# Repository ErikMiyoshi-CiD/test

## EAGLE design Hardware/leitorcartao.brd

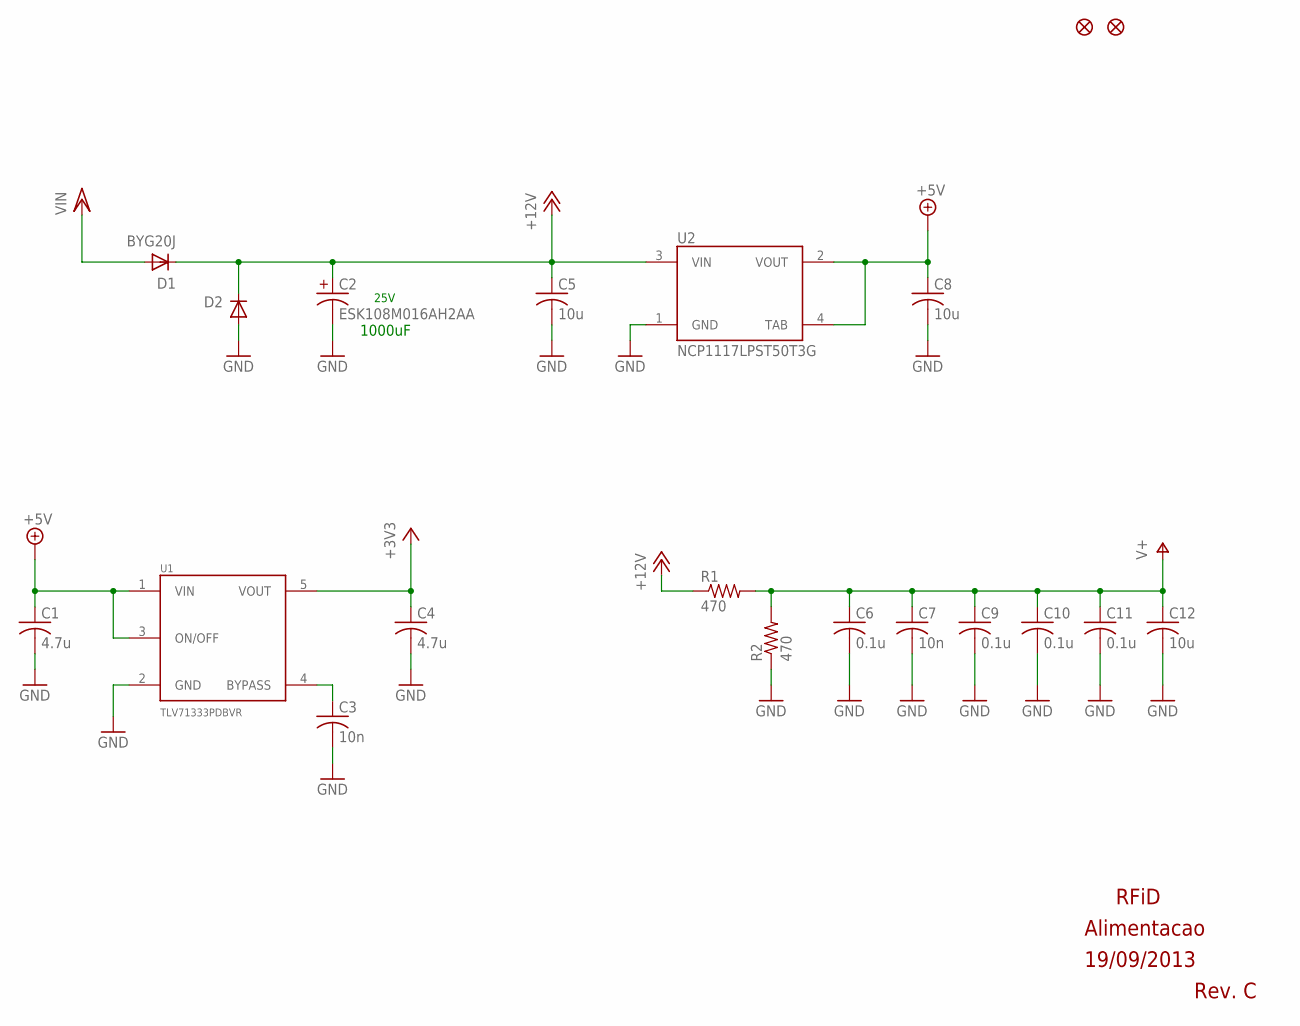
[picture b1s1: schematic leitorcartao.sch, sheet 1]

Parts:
C1, C4: 4.7u; C0603
C2: ESK108M016AH2AA
C3, C7: 10n; C0402
C5, C8, C12: 10u; C0805
C6, C9, C10, C11: 0.1u; C0402
D1: BYG20J; SMA
D2: DIODE-DO214AC; DO214AC
FID1, FID3: FIDUCIAL1.5X3; FIDUCIAL-1.5X3
R1, R2: 470; R0402
U1: TLV71333PDBVR; SOT-23-5
U2: NCP1117LPST50T3G; SOT223-3L

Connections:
+3V3: C4.1, U1.5 (VOUT); also elsewhere on the board
+5V: C1.1, C8.1, U1.1 (VIN), U1.3 (ON/OFF), U2.2 (VOUT), U2.4 (TAB); also elsewhere on the board
+12V: C2.+, C5.1, D1.K, D2.C, R1.1, U2.3 (VIN); also elsewhere on the board
GND: C1.2, C2.-, C3.2, C4.2, C5.2, C6.2, C7.2, C8.2, C9.2, C10.2, C11.2, C12.2, D2.A, R2.1, U1.2 (GND), U2.1 (GND); also elsewhere on the board
unnamed: C3.1, U1.4 (BYPASS)
V+: C6.1, C7.1, C9.1, C10.1, C11.1, C12.1, R1.2, R2.2; also elsewhere on the board
VCC/2: D1.A; also elsewhere on the board

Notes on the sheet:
RFiD
19/09/2013
Alimentacao
25V
1000uF
Rev. C

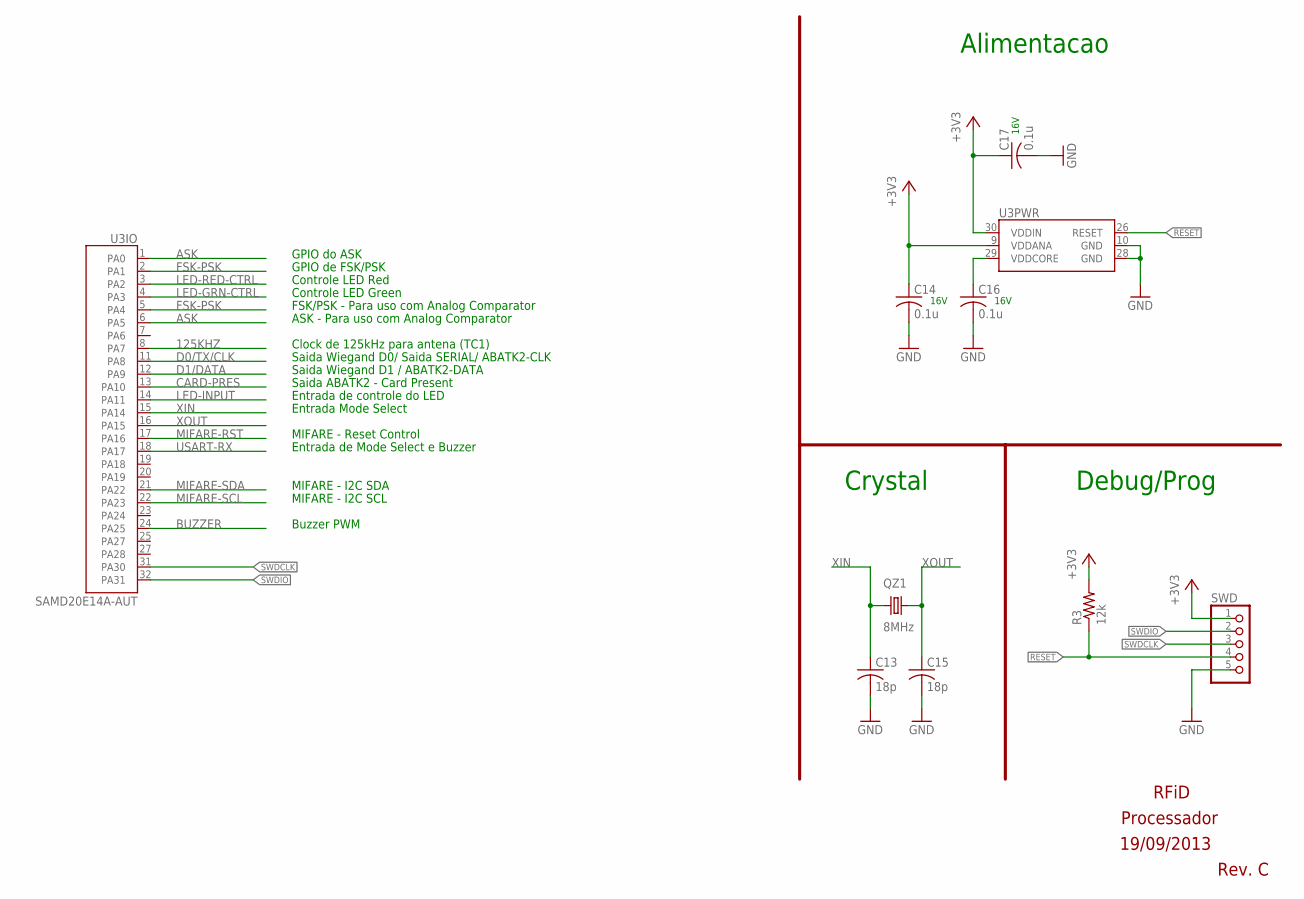
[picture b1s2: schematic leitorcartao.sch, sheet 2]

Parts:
C13, C15: 18p; C0603
C14, C16, C17: 0.1u; C0402
QZ1: 8MHz; HC49/S
R3: 12k; R0402
SWD: PINHD-1X5; 1X05
U3: SAMD20E14A-AUT; TQFP32

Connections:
125KHZ: U3.8 (PA7); also elsewhere on the board
+3V3: C14.1, C17.1, R3.2, SWD.1, U3.9 (VDDANA), U3.30 (VDDIN); also elsewhere on the board
ASK: U3.1 (PA0), U3.6 (PA5); also elsewhere on the board
BUZZER: U3.24 (PA25); also elsewhere on the board
CARD-PRES: U3.13 (PA10); also elsewhere on the board
D0/TX/CLK: U3.11 (PA8); also elsewhere on the board
D1/DATA: U3.12 (PA9); also elsewhere on the board
FSK-PSK: U3.2 (PA1), U3.5 (PA4); also elsewhere on the board
GND: C13.2, C14.2, C15.2, C16.2, C17.2, SWD.5, U3.10 (GND), U3.28 (GND); also elsewhere on the board
LED-GRN-CTRL: U3.4 (PA3); also elsewhere on the board
LED-INPUT: U3.14 (PA11); also elsewhere on the board
LED-RED-CTRL: U3.3 (PA2); also elsewhere on the board
MIFARE-RST: U3.17 (PA16); also elsewhere on the board
MIFARE-SCL: U3.22 (PA23); also elsewhere on the board
MIFARE-SDA: U3.21 (PA22); also elsewhere on the board
unnamed: C16.1, U3.29 (VDDCORE)
RESET: R3.1, SWD.4, U3.26 (RESET)
SWDCLK: SWD.3, U3.31 (PA30)
SWDIO: SWD.2, U3.32 (PA31)
USART-RX: U3.18 (PA17); also elsewhere on the board
XIN: C13.1, QZ1.1, U3.15 (PA14)
XOUT: C15.1, QZ1.2, U3.16 (PA15)

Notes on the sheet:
RFiD
19/09/2013
Processador
16V
Alimentacao
Debug/Prog
GPIO de FSK/PSK
Entrada Mode Select
Clock de 125kHz para antena (TC1)
Saida Wiegand D1 / ABATK2-DATA
GPIO do ASK
Controle LED Red
Controle LED Green
Saida Wiegand D0/ Saida SERIAL/ ABATK2-CLK
MIFARE - I2C SCL
MIFARE - I2C SDA
Saida ABATK2 - Card Present
Entrada de controle do LED
Rev. C
FSK/PSK - Para uso com Analog Comparator
Buzzer PWM
MIFARE - Reset Control
Crystal
Entrada de Mode Select e Buzzer
ASK - Para uso com Analog Comparator

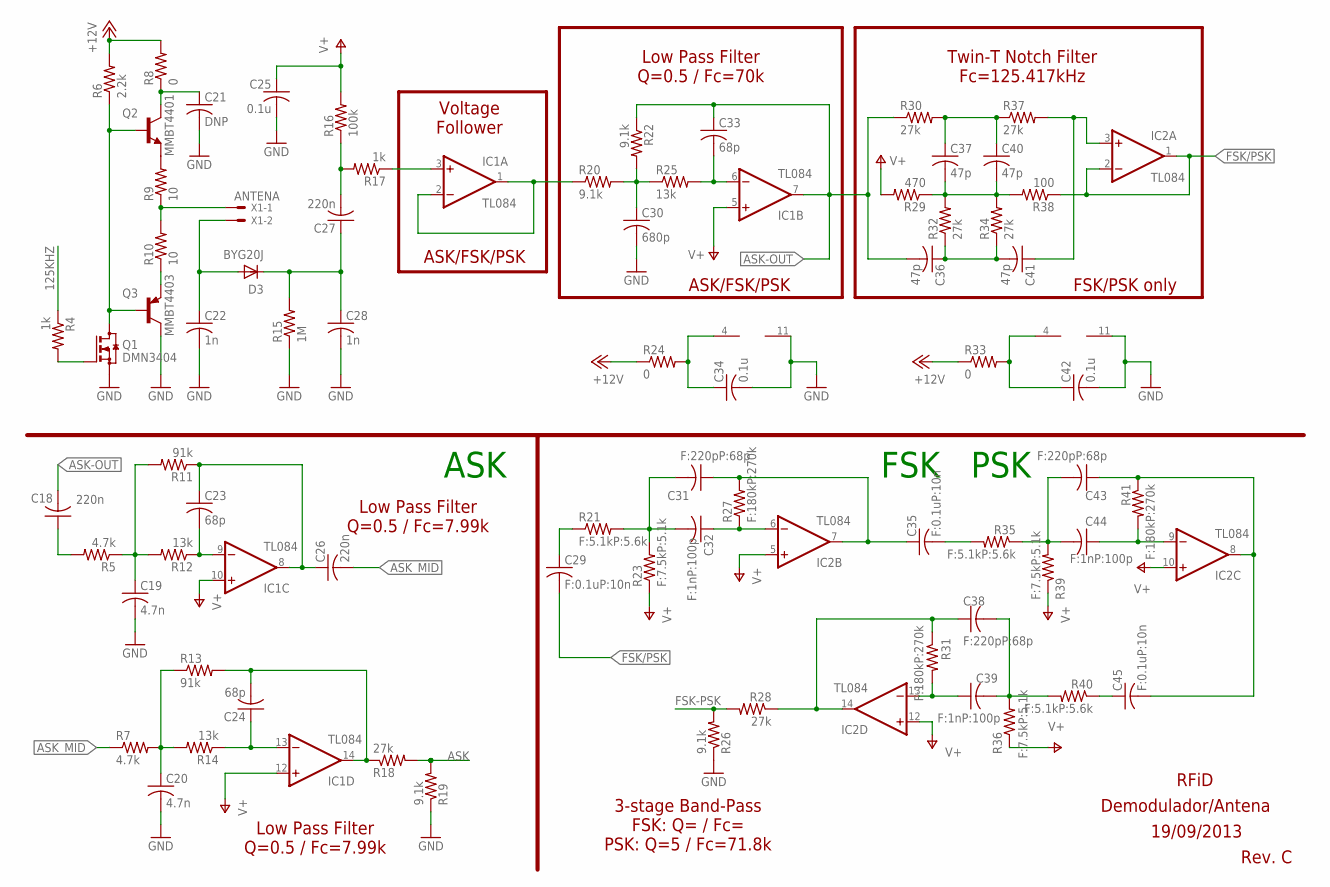
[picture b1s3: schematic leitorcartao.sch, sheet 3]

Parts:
C18, C26: 220n; C0402
C19, C20: 4.7n; C0402
C21: DNP; C0603
C22: 1n; C1812S
C23, C24, C33: 68p; C0402
C25, C34, C42: 0.1u; C0402
C27: 220n; C1206S
C28: 1n; C1206S
C29, C35, C45: F:0.1uP:10n; C0402
C30: 680p; C0402
C31, C38, C43: F:220pP:68p; C0402
C32, C39, C44: F:1nP:100p; C0402
C36, C37, C40, C41: 47p; C0402
D3: BYG20J; SMA
IC1, IC2: TL084; TSSOP14
Q1: DMN3404; SOT23
Q2: MMBT4401; SOT23
Q3: MMBT4403; SOT23
R4, R17: 1k; R0402
R5, R7: 4.7k; R0402
R6: 2.2k; R0402
R8, R24, R33: 0; R0402
R9, R10: 10; R0603
R11, R13: 91k; R0402
R12, R14, R25: 13k; R0402
R15: 1M; R1206S
R16: 100k; R0603
R18, R28, R30, R32, R34, R37: 27k; R0402
R19, R20, R22, R26: 9.1k; R0402
R21, R35, R40: F:5.1kP:5.6k; R0402
R23, R36, R39: F:7.5kP:5.1k; R0402
R27, R31, R41: F:180kP:270k; R0402
R29: 470; R0402
R38: 100; R0603
X1: ANTENA; 22-23-2021

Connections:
125KHZ: R4.1; also elsewhere on the board
+12V: R6.2, R8.2, R24.1, R33.1; also elsewhere on the board
ASK: R18.2, R19.2; also elsewhere on the board
ASK-OUT: C18.2, C33.1, C36.2, IC1.7 (OUT), R22.1, R30.1
ASK_MID: C26.2, R7.1
FSK-PSK: R26.2, R28.2; also elsewhere on the board
FSK/PSK: C29.2, IC2.1 (OUT), IC2.2 (-IN), R38.1
GND: C19.2, C20.2, C21.2, C22.2, C25.2, C28.2, C30.2, C34.2, C42.2, IC1.11 (V-), IC2.11 (V-), Q1.2 (S), Q3.3 (C), R15.1, R19.1, R26.1; also elsewhere on the board
unnamed: Q1.3 (D), Q2.1 (B), Q3.1 (B), R6.1
unnamed: Q1.1 (G), R4.2
unnamed: C22.1, D3.A, X1.2
unnamed: IC1.1 (OUT), IC1.2 (-IN), R20.1
unnamed: R9.1, R10.2, X1.1
unnamed: C30.1, R20.2, R22.2, R25.1
unnamed: C27.1, C28.1, D3.K, R15.2
unnamed: C27.2, R16.1, R17.2
unnamed: C33.2, IC1.6 (-IN), R25.2
unnamed: Q2.2 (E), R9.2
unnamed: C37.2, C40.2, R29.1, R32.2, R34.2, R38.2
unnamed: C37.1, C40.1, R30.2, R37.1
unnamed: C36.1, C41.2, R32.1, R34.1
unnamed: C18.1, R5.2
unnamed: C19.1, R5.1, R11.2, R12.2
unnamed: C41.1, IC2.3 (+IN), R37.2
unnamed: C38.1, IC2.14 (OUT), R28.1, R31.1
unnamed: C35.2, R35.2
unnamed: C39.1, IC2.13 (-IN), R31.2
unnamed: C23.2, IC1.9 (-IN), R12.1
unnamed: C31.2, C32.2, R21.2, R23.2
unnamed: C38.2, C39.2, R36.2, R40.2
unnamed: C45.1, R40.1
unnamed: C43.1, C45.2, IC2.8 (OUT), R41.1
unnamed: C21.1, Q2.3 (C), R8.1
unnamed: C34.1, IC1.4 (V+), R24.2
unnamed: C23.1, C26.1, IC1.8 (OUT), R11.1
unnamed: C42.1, IC2.4 (V+), R33.2
unnamed: IC1.3 (+IN), R17.1
unnamed: Q3.2 (E), R10.1
unnamed: C20.1, R7.2, R13.1, R14.2
unnamed: C24.1, IC1.13 (-IN), R14.1
unnamed: C29.1, R21.1
unnamed: C31.1, C35.1, IC2.7 (OUT), R27.2
unnamed: C32.1, IC2.6 (-IN), R27.1
unnamed: C43.2, C44.2, R35.1, R39.2
unnamed: C44.1, IC2.9 (-IN), R41.2
unnamed: C24.2, IC1.14 (OUT), R13.2, R18.1
V+: C25.1, IC1.5 (+IN), IC1.10 (+IN), IC1.12 (+IN), IC2.5 (+IN), IC2.10 (+IN), IC2.12 (+IN), R16.2, R23.1, R29.2, R36.1, R39.1; also elsewhere on the board

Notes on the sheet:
RFiD
19/09/2013
Demodulador/Antena
ASK
Rev. C
Voltage Follower
Low Pass Filter Q=0.5 / Fc=70k
Twin-T Notch Filter Fc=125.417kHz
ASK/FSK/PSK
FSK/PSK only
Low Pass Filter Q=0.5 / Fc=7.99k
3-stage Band-Pass FSK: Q= / Fc= PSK: Q=5 / Fc=71.8k
FSK
PSK

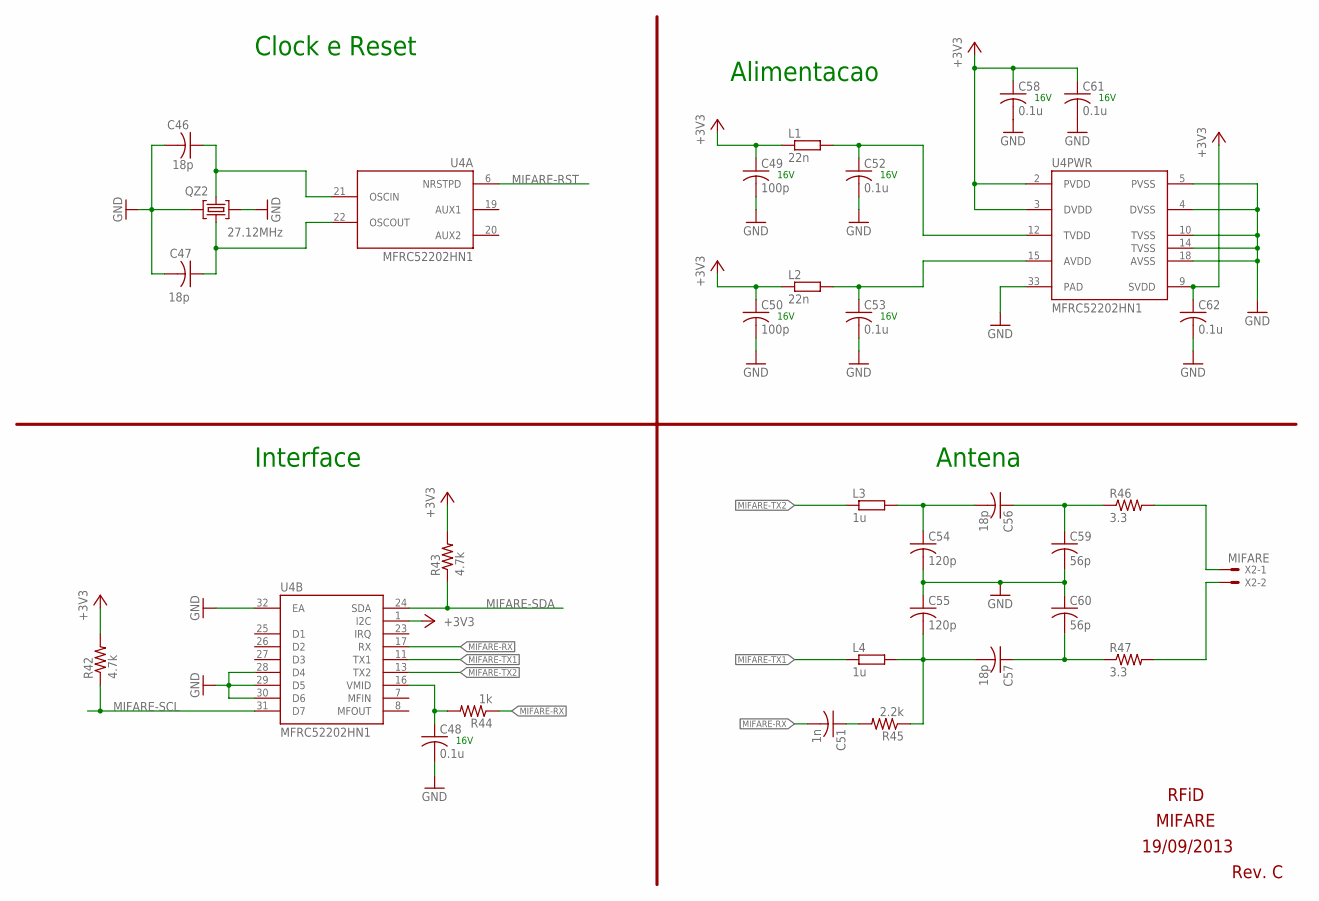
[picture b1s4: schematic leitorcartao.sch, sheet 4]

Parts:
C46, C47, C56, C57: 18p; C0603
C48, C52, C53, C58, C61, C62: 0.1u; C0402
C49, C50: 100p; C0402
C51: 1n; C0402
C54, C55: 120p; C0603
C59, C60: 56p; C0603
L1, L2: 22n; R0402
L3, L4: 1u; R0603
QZ2: 27.12MHz; CRISTAL4SMD
R42, R43: 4.7k; R0402
R44: 1k; R0402
R45: 2.2k; R0402
R46, R47: 3.3; R0603
U4: MFRC52202HN1; QFN32
X2: MIFARE; ANTENNA

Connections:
+3V3: C49.1, C50.1, C58.1, C61.1, C62.1, L1.1, L2.1, R42.2, R43.2, U4.1 (I2C), U4.2 (PVDD), U4.3 (DVDD), U4.9 (SVDD); also elsewhere on the board
GND: C46.2, C47.2, C48.2, C49.2, C50.2, C52.2, C53.2, C54.2, C55.1, C58.2, C59.2, C60.1, C61.2, C62.2, QZ2.2 (GND), QZ2.4 (GND), U4.4 (DVSS), U4.5 (PVSS), U4.10 (TVSS), U4.14 (TVSS), U4.18 (AVSS), U4.28 (D4), U4.29 (D5), U4.30 (D6), U4.32 (EA), U4.33 (PAD); also elsewhere on the board
MIFARE-RST: U4.6 (NRSTPD); also elsewhere on the board
MIFARE-RX: C51.2, R44.1, U4.17 (RX)
MIFARE-SCL: R42.1, U4.31 (D7); also elsewhere on the board
MIFARE-SDA: R43.1, U4.24 (SDA); also elsewhere on the board
MIFARE-TX1: L4.1, U4.11 (TX1)
MIFARE-TX2: L3.1, U4.13 (TX2)
unnamed: C52.1, L1.2, U4.12 (TVDD)
unnamed: C46.1, QZ2.3 (2), U4.21 (OSCIN)
unnamed: C53.1, L2.2, U4.15 (AVDD)
unnamed: C47.1, QZ2.1, U4.22 (OSCOUT)
unnamed: C55.2, C57.2, L4.2, R45.1
unnamed: C57.1, C60.2, R47.1
unnamed: C54.1, C56.2, L3.2
unnamed: C56.1, C59.1, R46.1
unnamed: C51.1, R45.2
unnamed: C48.1, R44.2, U4.16 (VMID)
unnamed: R46.2, X2.1
unnamed: R47.2, X2.2

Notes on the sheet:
RFiD
19/09/2013
MIFARE
16V
Antena
Alimentacao
Clock e Reset
Interface
Rev. C

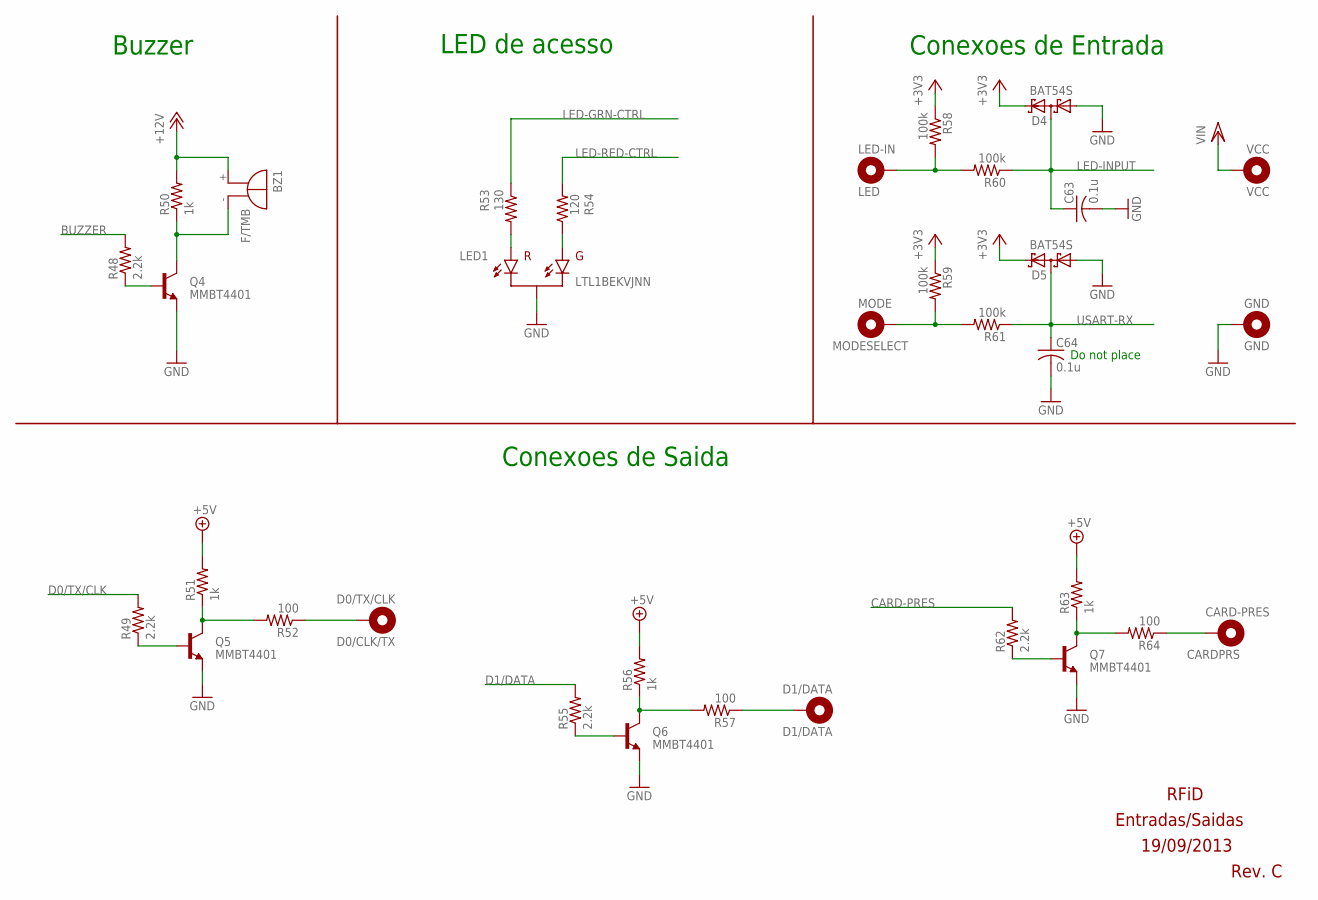
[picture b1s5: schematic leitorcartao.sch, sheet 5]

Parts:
BZ1: F/TMB
C63, C64: 0.1u; C0402
CARDPRS: CARD-PRES; HOLE
D0/TX/CLK: D0/CLK/TX; HOLE
D1/DATA: D1/DATA; HOLE
D4, D5: BAT54S; SOT23
GND: GND; HOLE
LED1: LTL1BEKVJNN
LED-IN: LED; HOLE
MODE: MODESELECT; HOLE
Q4, Q5, Q6, Q7: MMBT4401; SOT23
R48, R49, R55, R62: 2.2k; R0402
R50, R51, R56, R63: 1k; R0402
R52, R57, R64: 100; R0603
R53: 130; R0402
R54: 120; R0402
R58, R59, R60, R61: 100k; R0603
VCC: VCC; HOLE

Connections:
+3V3: D4.2 (C2), D5.2 (C2), R58.1, R59.1; also elsewhere on the board
+5V: R51.2, R56.2, R63.2; also elsewhere on the board
+12V: BZ1.+, R50.2; also elsewhere on the board
BUZZER: R48.2; also elsewhere on the board
CARD-PRES: R62.2; also elsewhere on the board
D0/TX/CLK: R49.2; also elsewhere on the board
D1/DATA: R55.2; also elsewhere on the board
GND: C63.2, C64.2, D4.1 (A1), D5.1 (A1), GND.P$1, LED1.COMMON, Q4.2 (E), Q5.2 (E), Q6.2 (E), Q7.2 (E); also elsewhere on the board
LED-GRN-CTRL: R53.1; also elsewhere on the board
LED-INPUT: C63.1, D4.3 (C1A2), R60.1; also elsewhere on the board
LED-RED-CTRL: R54.2; also elsewhere on the board
unnamed: Q6.1 (B), R55.1
unnamed: LED-IN.P$1, R58.2, R60.2
unnamed: Q5.1 (B), R49.1
unnamed: Q6.3 (C), R56.1, R57.2
unnamed: Q7.3 (C), R63.1, R64.2
unnamed: MODE.P$1, R59.2, R61.2
unnamed: Q7.1 (B), R62.1
unnamed: Q5.3 (C), R51.1, R52.2
unnamed: D0/TX/CLK.P$1, R52.1
unnamed: D1/DATA.P$1, R57.1
unnamed: CARDPRS.P$1, R64.1
unnamed: LED1.ANODE_RED, R53.2
unnamed: LED1.ANODE_GRN, R54.1
unnamed: BZ1.-, Q4.3 (C), R50.1
unnamed: Q4.1 (B), R48.1
USART-RX: C64.1, D5.3 (C1A2), R61.1; also elsewhere on the board
VCC/2: VCC.P$1; also elsewhere on the board

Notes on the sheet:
RFiD
19/09/2013
Entradas/Saidas
Conexoes de Saida
Conexoes de Entrada
LED de acesso
Buzzer
Rev. C
Do not place

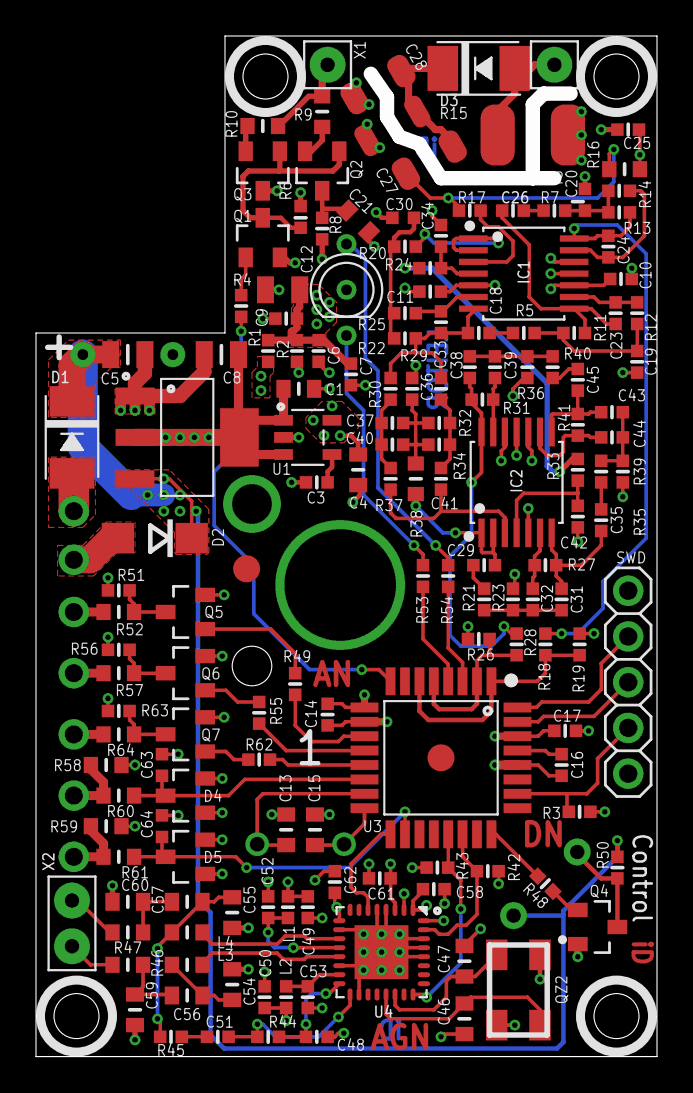
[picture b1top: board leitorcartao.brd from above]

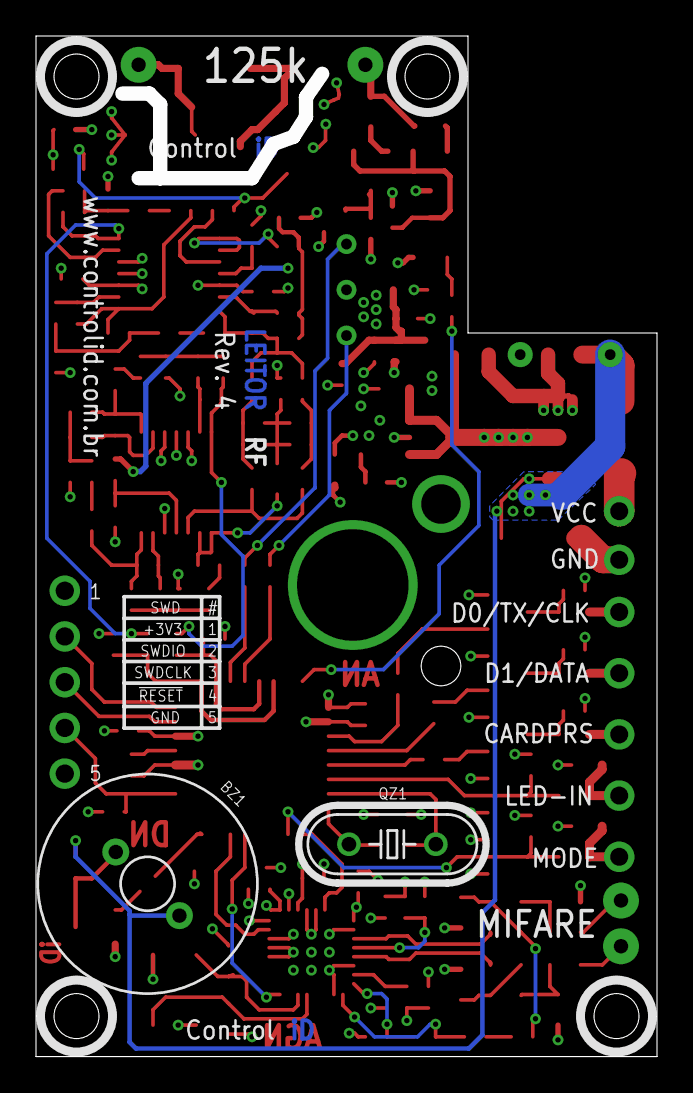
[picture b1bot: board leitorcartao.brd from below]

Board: 4 copper layers, 34.5 x 56.7 mm, 166 parts (2 on the bottom side), 98 nets.

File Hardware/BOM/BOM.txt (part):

Part	Value	Device	Package	Description	ASK	ASK_CUSTOMERPN	ASK_PN	CUSTOMERPN	FSK	FSK_PN	FSK_CUSTOMERPN	MIFARE	PASSIVO	MIFARE_PN	MIFARE_CUSTOMERPN	PN1	PSK	PSK_PN	SPECIAL	PSK_CUSTOMERPN
BZ1	F/TMB	F/TMB	F/TMB	BUZZER Source: Buerklin	X	BUZ-REP	PS1240P02BT		X	PS1240P02BT	BUZ-REP	X		PS1240P02BT	BUZ-REP		X	PS1240P02BT		BUZ-REP
C1	4.7u	C-USC0603	C0603	CAPACITOR, American symbol	X	C/4.7u/16V/C06	CL10A475KO8NNNC		X	CL10A475KO8NNNC	C/4.7u/16V/C06	X	Sim	CL10A475KO8NNNC	C/4.7u/16V/C06		X	CL10A475KO8NNNC		C/4.7u/16V/C06
C2	ESK108M016AH2AA	ESK108M016AH2AA	ESK108M016AH2AA		X	C/1m/16V/PTH	ESK108M016AH2AA		X	ESK108M016AH2AA	C/1m/16V/PTH	X	Sim	ESK108M016AH2AA	C/1m/16V/PTH		X	ESK108M016AH2AA		C/1m/16V/PTH
C3	10n	C-USC0402	C0402	CAPACITOR, American symbol	X	C/10n/50V/C04	CL05B103KB5NNNC		X	CL05B103KB5NNNC	C/10n/50V/C04	X	Sim	CL05B103KB5NNNC	C/10n/50V/C04		X	CL05B103KB5NNNC		C/10n/50V/C04
C4	4.7u	C-USC0603	C0603	CAPACITOR, American symbol	X	C/4.7u/16V/C06	CL10A475KO8NNNC		X	CL10A475KO8NNNC	C/4.7u/16V/C06	X	Sim	CL10A475KO8NNNC	C/4.7u/16V/C06		X	CL10A475KO8NNNC		C/4.7u/16V/C06
C5	10u	C-USC0805	C0805	CAPACITOR, American symbol	X	C/10u/25V/A08	GRM188R61E106MA73D		X	GRM188R61E106MA73D	C/10u/25V/A08	X	Sim	GRM188R61E106MA73D	C/10u/25V/A08		X	GRM188R61E106MA73D		C/10u/25V/A08
C6	0.1u	C-USC0402	C0402	CAPACITOR, American symbol	X	C/0.1u/16V/A04	CL05B104KO5NNNC		X	CL05B104KO5NNNC	C/0.1u/16V/A04	X	Sim	CL05B104KO5NNNC	C/0.1u/16V/A04		X	CL05B104KO5NNNC		C/0.1u/16V/A04
C7	10n	C-USC0402	C0402	CAPACITOR, American symbol	X	C/10n/50V/C04	CL05B103KB5NNNC		X	CL05B103KB5NNNC	C/10n/50V/C04	X	Sim	CL05B103KB5NNNC	C/10n/50V/C04		X	CL05B103KB5NNNC		C/10n/50V/C04
C8	10u	C-USC0805	C0805	CAPACITOR, American symbol	X	C/10u/25V/A08	GRM188R61E106MA73D		X	GRM188R61E106MA73D	C/10u/25V/A08	X	Sim	GRM188R61E106MA73D	C/10u/25V/A08		X	GRM188R61E106MA73D		C/10u/25V/A08
C9	0.1u	C-USC0402	C0402	CAPACITOR, American symbol	X	C/0.1u/16V/A04	CL05B104KO5NNNC		X	CL05B104KO5NNNC	C/0.1u/16V/A04	X	Sim	CL05B104KO5NNNC	C/0.1u/16V/A04		X	CL05B104KO5NNNC		C/0.1u/16V/A04
C10	0.1u	C-USC0402	C0402	CAPACITOR, American symbol	X	C/0.1u/16V/A04	CL05B104KO5NNNC		X	CL05B104KO5NNNC	C/0.1u/16V/A04	X	Sim	CL05B104KO5NNNC	C/0.1u/16V/A04		X	CL05B104KO5NNNC		C/0.1u/16V/A04
C11	0.1u	C-USC0402	C0402	CAPACITOR, American symbol	X	C/0.1u/16V/A04	CL05B104KO5NNNC		X	CL05B104KO5NNNC	C/0.1u/16V/A04	X	Sim	CL05B104KO5NNNC	C/0.1u/16V/A04		X	CL05B104KO5NNNC		C/0.1u/16V/A04
C12	10u	C-USC0805	C0805	CAPACITOR, American symbol	X	C/10u/25V/A08	GRM188R61E106MA73D		X	GRM188R61E106MA73D	C/10u/25V/A08	X	Sim	GRM188R61E106MA73D	C/10u/25V/A08		X	GRM188R61E106MA73D		C/10u/25V/A08
C13	18p	C-USC0603	C0603	CAPACITOR, American symbol	X	C/18p/50V/D06	CL05C180JB5NNNC		X	CL05C180JB5NNNC	C/18p/50V/D06	X	Sim	CL05C180JB5NNNC	C/18p/50V/D06		X	CL05C180JB5NNNC		C/18p/50V/D06
C14	0.1u	C-USC0402	C0402	CAPACITOR, American symbol	X	C/0.1u/16V/A04	CL05B104KO5NNNC		X	CL05B104KO5NNNC	C/0.1u/16V/A04	X	Sim	CL05B104KO5NNNC	C/0.1u/16V/A04		X	CL05B104KO5NNNC		C/0.1u/16V/A04
C15	18p	C-USC0603	C0603	CAPACITOR, American symbol	X	C/18p/50V/D06	CL05C180JB5NNNC		X	CL05C180JB5NNNC	C/18p/50V/D06	X	Sim	CL05C180JB5NNNC	C/18p/50V/D06		X	CL05C180JB5NNNC		C/18p/50V/D06
C16	0.1u	C-USC0402	C0402	CAPACITOR, American symbol	X	C/0.1u/16V/A04	CL05B104KO5NNNC		X	CL05B104KO5NNNC	C/0.1u/16V/A04	X	Sim	CL05B104KO5NNNC	C/0.1u/16V/A04		X	CL05B104KO5NNNC		C/0.1u/16V/A04
C17	0.1u	C-USC0402	C0402	CAPACITOR, American symbol	X	C/0.1u/16V/A04	CL05B104KO5NNNC		X	CL05B104KO5NNNC	C/0.1u/16V/A04	X	Sim	CL05B104KO5NNNC	C/0.1u/16V/A04		X	CL05B104KO5NNNC		C/0.1u/16V/A04
C18	220n	C-USC0402	C0402	CAPACITOR, American symbol	X	C/220n/25V/C04	C1005X5R1E224K050BC						Sim							
C19	4.7n	C-USC0402	C0402	CAPACITOR, American symbol	X	C/4.7n/25V/D04	CL05B472KA5NNNC						Sim							
C20	4.7n	C-USC0402	C0402	CAPACITOR, American symbol	X	C/4.7n/25V/D04	CL05B472KA5NNNC						Sim							
C21	DNP	C-USC0805	C0805	CAPACITOR, American symbol	X	DNP			X	DNP	DNP		Sim				X	DNP		
C22	1n	C-USC1812	C1812	CAPACITOR, American symbol	X	C/1n/500V/E18	C1812C102FBGACTU		X	C1812C102FBGACTU	C/1n/500V/E18		Sim				X	C1812C102FBGACTU		C/1n/500V/E18
C23	68p	C-USC0402	C0402	CAPACITOR, American symbol	X	C/68p/25V/D04	CL05C680JB5NNNC													
C24	68p	C-USC0402	C0402	CAPACITOR, American symbol	X	C/68p/25V/D04	CL05C680JB5NNNC													
C25	0.1u	C-USC0402	C0402	CAPACITOR, American symbol	X	C/0.1u/16V/A04	CL05B104KO5NNNC		X	CL05B104KO5NNNC	C/0.1u/16V/A04		Sim				X	CL05B104KO5NNNC		C/0.1u/16V/A04
C26	220n	C-USC0402	C0402	CAPACITOR, American symbol	X	C/220n/25V/C04	C1005X5R1E224K050BC						Sim							
C27	220n	C-USC1206	C1206	CAPACITOR, American symbol	X	C/220n/200V/C12	C3216X7T2E224K160AA		X	C3216X7T2E224K160AA	C/220n/200V/C12		Sim				X	C3216X7T2E224K160AA		C/220n/200V/C12
C28	1n	C-USC1206	C1206	CAPACITOR, American symbol	X	C/1n/200V/C12	CL31C102JHHNFNE		X	CL31C102JHHNFNE	C/1n/200V/C12		Sim				X	CL31C102JHHNFNE		C/1n/200V/C12
C29	F:0.1uP:10n	C-USC0402	C0402	CAPACITOR, American symbol					X	CL05B104KO5NNNC			Sim				X	CL05B103KB5NNNC		C/0.1u/16V/A04
C30	680p	C-USC0402	C0402	CAPACITOR, American symbol	X	C/680p/25V/C04	CL05B681KB5NNNC		X	CL05B681KB5NNNC	C/680p/25V/C04		Sim				X	CL05B681KB5NNNC		C/680p/25V/C04
C31	F:220pP:68p	C-USC0402	C0402	CAPACITOR, American symbol					X	CL05C221JB5NNNC	C/220p/25V/D04		Sim				X	CL05C680JB5NNNC		C/68p/25V/D04
C32	F:1nP:100p	C-USC0402	C0402	CAPACITOR, American symbol					X	C0402C102J1GACTU	C/1n/100V/D04		Sim				X	CL05C101JB5NNNC		C/100p/50V/D04
C33	68p	C-USC0402	C0402	CAPACITOR, American symbol	X	C/68p/25V/D04	CL05C680JB5NNNC		X	CL05C680JB5NNNC	C/68p/25V/D04		Sim				X	CL05C680JB5NNNC		C/68p/25V/D04
C34	0.1u	C-USC0402	C0402	CAPACITOR, American symbol	X	C/0.1u/16V/A04	CL05B104KO5NNNC		X	CL05B104KO5NNNC	C/0.1u/16V/A04		Sim				X	CL05B104KO5NNNC		C/0.1u/16V/A04
C35	F:0.1uP:10n	C-USC0402	C0402	CAPACITOR, American symbol					X	CL05B104KO5NNNC	C/0.1u/16V/A04		Sim				X	CL05B103KB5NNNC		C/10n/50V/C04
C36	47p	C-USC0402	C0402	CAPACITOR, American symbol					X	GRM1555C1H470FA01D	C/47p/25V/E04		Sim				X	GRM1555C1H470FA01D		C/47p/25V/E04
C37	47p	C-USC0402	C0402	CAPACITOR, American symbol					X	GRM1555C1H470FA01D	C/47p/25V/E04		Sim				X	GRM1555C1H470FA01D		C/47p/25V/E04
C38	F:220pP:68p	C-USC0402	C0402	CAPACITOR, American symbol					X	CL05C221JB5NNNC	C/220p/25V/D04		Sim				X	CL05C680JB5NNNC		C/68p/25V/D04
C39	F:1nP:100p	C-USC0402	C0402	CAPACITOR, American symbol					X	C0402C102J1GACTU	C/1n/100V/D04		Sim				X	CL05C101JB5NNNC		C/100p/50V/D04
C40	47p	C-USC0402	C0402	CAPACITOR, American symbol					X	GRM1555C1H470FA01D	C/47p/25V/E04		Sim				X	GRM1555C1H470FA01D		C/47p/25V/E04
C41	47p	C-USC0402	C0402	CAPACITOR, American symbol					X	GRM1555C1H470FA01D	C/47p/25V/E04		Sim				X	GRM1555C1H470FA01D		C/47p/25V/E04
C42	0.1u	C-USC0402	C0402	CAPACITOR, American symbol	X	C/0.1u/16V/A04	CL05B104KO5NNNC		X	CL05B104KO5NNNC	C/0.1u/16V/A04		Sim				X	CL05B104KO5NNNC		C/0.1u/16V/A04
C43	F:220pP:68p	C-USC0402	C0402	CAPACITOR, American symbol					X	CL05C221JB5NNNC	C/220p/25V/D04		Sim				X	CL05C680JB5NNNC		C/680p/25V/C04
C44	F:1nP:100p	C-USC0402	C0402	CAPACITOR, American symbol					X	C0402C102J1GACTU	C/1n/100V/D04		Sim				X	CL05C101JB5NNNC		C/100p/50V/D04
C45	F:0.1uP:10n	C-USC0402	C0402	CAPACITOR, American symbol					X	CL05B104KO5NNNC	C/0.1u/16V/A04		Sim				X	CL05B103KB5NNNC		C/10n/50V/C04
C46	18p	C-USC0603	C0603	CAPACITOR, American symbol								X	Sim	CL05C180JB5NNNC	C/18p/50V/D06					
C47	18p	C-USC0603	C0603	CAPACITOR, American symbol								X	Sim	CL05C180JB5NNNC	C/18p/50V/D06					
C48	0.1u	C-USC0402	C0402	CAPACITOR, American symbol								X	Sim	CL05B104KO5NNNC	C/0.1u/16V/A04					
C49	100p	C-USC0402	C0402	CAPACITOR, American symbol								X	Sim	CL05C101JB5NNNC	C/100p/50V/D04					
C50	100p	C-USC0402	C0402	CAPACITOR, American symbol								X	Sim	CL05C101JB5NNNC	C/100p/50V/D04					
C51	1n	C-USC0402	C0402	CAPACITOR, American symbol								X	Sim	C0402C102J1GACTU	C/1n/100V/D04					
C52	0.1u	C-USC0402	C0402	CAPACITOR, American symbol								X	Sim	CL05B104KO5NNNC	C/0.1u/16V/A04					
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
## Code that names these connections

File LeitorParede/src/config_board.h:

/*
 * config_board.h
 *
 * Created: 02/07/2013 10:21:04
 *  Author: Neto
 */ 
#include <asf.h>

#ifndef CONFIG_BOARD_H_
#define CONFIG_BOARD_H_

#define INTMASK2 2 // Pino da PORTD que receberá a interrupção do ASK e FSK
#define INTMASK6 6 // Pino da PORTC que receberá a interrupção do PSK

#define INT2IF 2 // Flag da interrupção do pino de ASK_FSK
#define INT6IF 6 // Flag da interrupção do pino de PSK

#define LED_GREEN (IOPORT_CREATE_PIN(PORTD,5))		// Pino de saída para controle do LED Verde de acesso
#define BUZZER (IOPORT_CREATE_PIN(PORTD,3))			// Pino de saída para geração de frequência do Buzzer
#define RELAY (IOPORT_CREATE_PIN(PORTC,4))			// Pino de saída para controle da bobina do relé
#define RFID_CLK (IOPORT_CREATE_PIN(PORTC,3))		// Pino de saída para geração do clock de 125kHz excitador da antena
#define ASK_FSK (IOPORT_CREATE_PIN(PORTD,2))		// Pino de entrada para recepção do sinal filtrado ASK e PSK
#define CARD_PRES (IOPORT_CREATE_PIN(PORTR,1))		// Pino de saída para sinalização de presença de cartão no protocolo ABATK2 (Card Present)
#define USART_TX_PIN IOPORT_CREATE_PIN(PORTD, 7)	// Pino de saída para envio dos dados de Wiegand (D0), TX (Serial) e CLK (ABATK2).
#define D1_DATA IOPORT_CREATE_PIN(PORTC,0)			// Pino de saída para envio dos dados de Wiegand (D1)
#define LED_IN IOPORT_CREATE_PIN(PORTC,7)			// Pino de entrada para sinalização de que o cartão foi aceito e a entrada foi liberada
#define PSK_PIN (IOPORT_CREATE_PIN(PORTC,6))			// Pino de entrada para recepção do sinal filtrado PSK

#define USART_SERIAL               &USARTD0					// Serial utilizada para transmistir
#define USART_SERIAL_BAUDRATE      115200					// Velocidade de transmissao
#define USART_SERIAL_LENGTH        USART_CHSIZE_8BIT_gc		// Tamanho do frame de dados
#define USART_SERIAL_PARITY        USART_PMODE_DISABLED_gc	// Sem paridade
#define USART_SERIAL_STOP_BIT      0						// 1 bit de parada

void Inicializa_USART(void);

void Inicializa_Placa(void);

void Liga_Buzzer(uint16_t period);
void Conf_Buzzer(void);
void Desliga_Buzzer(void);

void Liga_125kHz(void);

void Inicializa_GPIO(void);
void ASK_Pin_Config(void);
void FSK_Pin_Config(void);
void PSK_Pin_Config(void);
void Clear_PORTD_Int_Flag(void);
void Clear_PORTC_Int_Flag(void);

void Liga_Timer_XCL_16bits(void);
void Desliga_Timer_XCL_16bits(void);
void Conf_Timer_XCL_16bits(void);
uint16_t  Cont_Timer_XCL_16bits(void);

void Liga_TC5(void);
void Desliga_TC5(void);
void Configura_TC5(void);
uint16_t Ler_Contagem_TC5(void);
void Reinicia_Contagem_TC5(void);
void TC5_Set_CountUp_Mode(void);

#endif /* CONFIG_BOARD_H_ */

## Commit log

2013-07-11 Segundo commit inicial.
2013-07-12 Criadas funções de envio por serial. Protocolos de envio finalizados (Wiegand, ABATRK2 e Serial).
2013-07-12 Documentação de vários arquivos e funções. Início da elaboração da rotina de decodificação de FSK.
2013-07-15 Início do FSK
2013-07-15 Começando a ler FSK
2013-07-19 Camada física do PSK decodificada, falta entender os dados recebidos.
2013-07-22 Inciada a adaptação do código para versão de produção.
2013-07-22 Nova versão do código para produção e início da implementação do ADC para teclado capacitivo.
2013-07-23 PSK funcionando.
2013-07-23 Inclusão dos arquivos de Hardware.
2013-07-25 Firmware com o limitador de leituras sequenciais.
    Não portável pois usa o XCL do XMegaE.
2013-07-26 SMD20 criado na biblioteca RFiD do EAGLE.
2013-07-29 Nova versão da placa do leitor de parede. Em progesso.
2013-07-30 Mudanças de packages e início de roteamento.
2013-07-30 Mais progressos, próximo do final.
2013-07-30 Roteamento finalizado. Verificar posiconamento.
    Espessuras de trilhas precisam ser revisadas.
2013-08-01 Versão da leitora com as alterações solicitadas e outras.
2013-08-01 Próximo RC de versão de versão final.
2013-08-02 Nova versão do leitor. Aguardando revisão.
2013-08-02 Alterações solicitadas por Albert. Aguradando David.
2013-08-02 Pequenas alterações de notação de valores dos componentes.
    Início do BOM.
2013-08-05 Nova versão com as alterações sugeridas por Albert e David.
    Componentes da antena do MIFARE alterados para 0603.
2013-08-05 Nova versão com a sugestão de um filtro RC na alimentação da antena.
    Criado o modelo 3D.
2013-08-05 Alterações do valor dos divisores resisitivos.
    Coloção de 4 furos de fontagem M2.
    Troca do LED PLCC4 por um mais barato.
2013-08-06 Versão do modelo da placa finalizado.
2013-08-06 Criados polígonos de alimentação.
    Correção dos comentários nas páginas do esquema elétrico.
2013-08-06 Arquivos 3D finalizados.
    Início do Bill of Materials.
2013-09-06 Início da versão 3.0
2013-09-06 Novas alterações do esquema do RFID. ASK com valores já calculados.
2013-09-06 Finalização do esquema do RFID, falta valores de PSK e FSK.
2013-09-06 Correção de conexões dos OpAmps.
    Alteração de valores do ASK.
    Correções na topologia do PSK.
2013-09-09 Adicionadas duas novas camadas na placa.
    Layer 4 -> Power Plane
    Layer 5 -> Ground Plane
2013-09-11 Mudanças na placa.
    Inclusão do LED Red/Green.
2013-09-13 Mudanças no layout.
2013-09-17 Nova versão do roteamento. Tentativa de isolar tudo no top para DFM.
2013-09-17 Mais progressos em isolar todos os componentes na camada superior.
2013-09-17 Todos os componentes posicionados no Top.
2013-09-17 Última versão do posicionamento.
2013-09-18 Novo firmware para SAMD20 sem ASF
2013-09-18 Roteamento finalizado, polígonos criados e silks criados.
    Necessita revisão.
2013-09-18 Inícios dos trabalhos na BOM do leitor de parede.
    Otimização de componentes sendo realizada em conjunto com a elaboração da BOM.
2013-09-19 BOM e layout finalizados, esquema renumerado.
2013-09-20 Alteração de um package no filtro NOTCH para redução de SKU.
    Otimização de posicionamento de dois capacitores.
2013-09-23 Ajuste do silkscreen na placa.
2013-09-23 Commit do eagle.epf
2013-09-24 Mudança das linhas de dimensão do capacitor eletrolítoco para tDocu.
2013-09-24 Inclusão dos scripts para painéis e correção de um angle na placa. FALTA INCLUIR FIDUCIAIS
2013-09-24 Correção de algum pau de nomenclatura de Posição_LED.png
2013-09-24 Documentos para fabricação
2013-09-24 Mudanças de packages e valores para otimização de BOM.
    Adição dos fiduciais.
    Alterações feitas baseadas na revisão do commit 286c1a7f
2013-09-24 Início da BOM
2013-09-24 Mais algumas otimizações de BOM.
2013-09-24 Alteração de packages e valores de capacitores para otimizar a BOM.
2013-09-24 Fim das perfumarias no silkscreen.
2013-09-24 Commit final antes de panelizar
2013-09-24 Commit parcial. Fim da panelização.
2013-09-24 Commit final como enviado para JOY
2013-10-02 Inclusão de imagens
2013-10-09 Adição de novas colunas para controle de versão de pedidos.
2013-10-10 Novas alterações na BOM. Ainda sem os filtro de PSK e FSK.
2013-10-10 Nova versão da BOM, análise dos componentes parou nos resistores de valor de 12k.
2013-10-11 Finalização da BOM pelo Neto.
    Alteração de customers PN errados.
    Alteração de PN errados.
    Seleção de componentes mais baratos.
    Candidato para envio à AVNET.
2013-10-11 Correção de erros na BOM.
2013-10-11 Adição dos valores dos componentes dos filtros PSK/FSK.
    Adição dos PN dos componentes dos filtros.
2013-10-14 Novos campos adicionados na BOM para facilitar o pedido.
2013-10-14 Novas alterações na BOM com correção de campos errados.
2013-10-14 Alteração de PN para componentes Samsung.
2013-10-14 Planilha de pedido para check
2013-10-14 Pedido AVNET
2013-10-14 Mudanças nos PN dos reguladores de tensão.
2013-10-15 Nova BOM com ACCURA em todas outras modulações.
2013-10-15 Commit com o EAGLE salvo dessa vez.
2013-10-15 Bom final para pedido AVNET
2013-10-17 Adição dos comandos de show para conferência das diferentes montagens do leitor. Rever se está tudo ok.
2013-10-17 Correção nome da BOM
2013-11-08 Primeiro commit do Luiz! Funciona o buzzer
2013-11-14 Implementação e teste ABA-TRAK e Wiegand
    Modularização das funções
    Próximas tarefas:
    Implementar o delay em tempo real
    Implementar o Serial Out
2013-11-27 BOM do protótipo da versão final da placa finalizado.
2013-11-28 BOM com capacitores mais baratos e com componentes que já temos na Control iD.
2013-11-28 Troca do capacitor do circuito tanque que estava fora de estoque.
2013-12-02 BOM do protótipo v3 e início da alteração do layout para os novos parafusos.
2013-12-03 Primeira solução para o posicionamento dos componentes e furos corrigidos.
2013-12-04 Nova solução de posicionamento dos compoentes no leitor.
2013-12-04 Novas ideias para aumentar a isolação de alta tensão.
2013-12-13 Ajustes no silk das placas.
2013-12-13 Aumento nos furos de cinta plástica e do furo do cabo.
2013-12-13 Ajustes no silk screen do leitor.
2013-12-13 Ajustes de silk e trilhas.
2013-12-13 Correção de conflitos entre tNames e tStop.
2013-12-13 Início da documentação de fabricação do Leitor RF.
2013-12-15 Commit logo antes de panelizar
2013-12-15 Arquivos panelizados. Fim. Conforme enviado para Joy.
2013-12-20 Criado Excel de BOM e XY do versão atual do Leitor (placa com furos errados).
2013-12-20 Impressão de nomes para conferência da Eurotronics.
2014-01-20 Documentos da Eurotronics para orçamento e montagem.
2014-02-21 Stencil e painel conforme JOY!
2014-02-24 Agora vai... Usa oscilador de 8MHz externo e habilita o 125kHz além de configurar pinos e inicializar o delay_s, delay_ms e delay_us.
2014-02-25 Está lendo ASK com sucesso.
2014-02-26 Já permite programação do modo (precisa testar)
2014-02-26 Início do Mifare
2014-02-27 Mifare funciona! Ainda precisa otimizar I2C
2014-02-28 Agora funciona!
2014-02-28 Agora lê e lê rápido!
2014-02-28 Funciona tudo!
2014-03-05 Work in Progress. Já tem WDT e anti duplo cartão. FALTA TESTAR
2014-03-07 Timeout funciona! Vamos para as cabeças.
2014-03-07 Watchdog funciona lindamente com timeout de 3.4s -- Mais que suficiente
2014-03-07 Idle é RED! Fim
2014-03-18 Correção da paridade! Agora vai para a feira
2014-03-18 Correção do cálculo de paridade.
2015-07-13 Firmware Anatel (não é garantido que seja o mais novo)
2015-07-13 Pronto para Txai.
2015-07-14 Firmware Anatel, versão final
2016-04-26 Inicio do projeto do iDProx rev2 no Altium.
2016-04-27 Esquema para revisão.
2016-07-21 Início LeitorRFV3
2016-07-21 Pronto para início de Javier.
2016-07-27 Firmware V3 com novas bibliotecas
2016-08-01 V2.0. Atualização do gitignore.
2016-08-01 BOM do leitor.
2016-08-01 Lê configurações na memória.
2016-08-04 Deve funcionar bem agora!
2016-08-07 WIP mifare.
2016-08-07 PCB V2.1
2016-08-08 Funciona!
2016-08-08 Release candidate da V2.1
2016-08-08 Correção de gitignore
2016-08-08 V2.1 oficial
2016-08-09 WDT=8s / CARD_REPEAT=300ms / URNA_REPEAT=3s
2016-08-09 V2.2 binário
2017-05-01 Suporte a Wiegand 26 e 34.
2017-05-01 Pequena gambiarra para não precisar reescrever o programador.
2017-07-11 Commit antes de mudar coisas
2017-07-11 Inclusão de Wiegand 66
2017-07-11 Inclusão dos arquivos finais
2017-09-18 XOSC corrige o jitter do DFLL!
2017-09-19 Correção do auto-gain do XTAL
2017-09-19 Agora vai! XOSC só controla 125kHZ e amostragem. DFLL roda no OSC8M para não reiniciar.
2017-09-19 Release 2017.09.18
2017-11-09 WIP. Alterando o layout com os furos corrigidos.
2017-11-12 Inclusão do firmware da DEV Tecnologia
2017-11-23 Placement finalizado. Falta rotear.
2017-11-24 Placa praticamente finalizada. Falta arrumar problema de polígono na Top Layer.
2017-12-05 Placa finalizada para revisão.
2017-12-07 Duas versões da Dev no Git.
2017-12-12 Exlusão dos arquivos do iDTouch que não pertencem ao projeto. Ajuste de biblioteca e PCB.
2018-01-23 Gerbers para fabricação da versão 2.2.
2018-02-23 Firmware e alterações da placa
2018-02-23 Version bump do iDProx de 2.2 para 2.3. Ajustes mínimos no painel para cotação e fabricação de lote piloto.
2018-04-05 Ajuste do Vault para contemplar o R/1/5%/04 e inclusão de um arquivo de BOM.
2018-04-23 Firmware final KIM
2018-04-23 commit source
2019-05-20 Change Wiegand D0 and D1 pins definitions - Change Wiegand D0 and D1 pins, making them compliant with iD Prox's controllers. - ABATK2 and RS232 output modes remain unchanged, and so does output mode 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
2019-05-20 Adição dos arquivos de manual e guia rápido.
2019-05-20 Set first Wiegand size according to RF module - Sets first Wiegand output to 34 bits if Mifare module is detected, and 26 bits otherwise.
2019-05-29 remoção de arquivos gerados e pasta de deploy
2019-05-29 Version bump e zip
2019-06-03 Add version 2.5 of Quick Guides - Changed Wiegand pins D0 and D1 annotations on Quick Guides.
2019-07-03 Adicionada no guia rápido a instrução para não instalar o aparelho em locais onde há objetos metálicos.
2019-07-03 Adição da configuração para 66 bits no guia rápido em português
2019-07-05 Add Wiegand 32-bits mode - Implement Wiegand 32-bits mode (without parities).
2019-07-08 Adição da configuração wiegand 32 bits
2019-07-12 Firmware 1.4.0
2020-03-19 Inversão dos Labels D0 e D1 no esquemático para manter a coerência com a última versão de firmware do iDProx.
2020-07-20 Adjust buzzer PWM frequency and Mifare driver impedance (v1.5.0) - Update buzzer PWM frequency to 2.7kHz. - Improve Mifare driver output impedance to its lowest value.
2021-09-13 V1.7.0: Resets REPMIF as soon as iDProx boots (RF_Mifare.c)
    All other files were changes to remover warnings from the compiler in MDK535.EXE (Keil uVision)
2022-10-02 V1.8.0 - Corrige comportamento na serial (idle = 1 em RS-232 TTL)
2022-10-13 V1.8.1 - Corrige tudo de RS-232 TTL. Tinha muitos erros.
2022-10-13 Small fix. V1.8.1.
2023-03-10 add copper to idprox-panel for laser serial
2023-03-14 Ajustes no painel
    -Aumento das abas para 7.5mm
    -Ajuste no cobre nas abas do painel
    -Gerbers atualizados
2023-07-12 Adição de 3D genérico do capacitor eletrolítico e 3D da KSAV2 com heardes genéricos
2023-08-14 HW versão V2.4 - Adição do resistor R26 de 430 Ohm no 5V
    -Email de referência "ECN - iDProx"
    -Gerbers gerados
2023-09-25 change gerbers description to lead free
